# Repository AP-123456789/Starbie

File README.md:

# Starbie

Starbie is a custom embedded electronics project built around the Seeed Studio XIAO ESP32-C3 (RISC-V). It combines a Seeed XIAO ESP32-C3, a DHT11 temperature and humidity sensor, an MPU6050 IMU, a 0.96-inch I2C OLED display, and two push buttons on a custom two-layer PCB designed from scratch in KiCad.

## Hardware Components

* **Microcontroller:** [Seeed Studio XIAO ESP32-C3](https://wiki.seeedstudio.com/SeeedStudio_XIAO_ESP32C3/) (RISC-V 32-bit RISC-V single-core CPU, Wi-Fi, BLE)
* **Display:** 0.96-inch I2C Monochrome OLED Display (128x64 resolution, SSD1306 driver)
* **Temperature/Humidity Sensor:** [DHT11 Sensor](https://www.component101.com/sensors/dht11-temperature-and-humidity-sensor) with a $10\text{ k}\Omega$ pull-up resistor on the data line
* **Motion Sensor:** MPU6050 6-axis Accelerometer & Gyroscope
* **User Input:** 2x Tactile push buttons
* **Expansion:** 1x4 and 1x8 pin headers

## Repository Structure

```
starbie/
├── Firmware/
│   ├── include/
│   ├── lib/
│   ├── src/
│   │   └── main.cpp          # Core C++ firmware
│   └── platformio.ini        # PlatformIO build configuration
├── Hardware/
│   ├── startbie.kicad_sch    # Schematic capture file
│   ├── startbie.kicad_pcb    # PCB layout file
│   ├── startbie.kicad_pro    # KiCad project file
│   └── Gerbers/              # Manufacturing files
└── README.md
```

## Firmware & Toolchain

The firmware is written in C++ using the Arduino framework via PlatformIO in VS Code. It handles I2C communication with the OLED display while polling the push buttons and reading sensor data.

### Dependencies
* [Adafruit SSD1306 Library](https://github.com/adafruit/Adafruit_SSD1306)
* [Adafruit GFX Library](https://github.com/adafruit/Adafruit-GFX-Library)

---

## 10-Hour Build Log

### Hour 1: Environment Setup and Error 10013
I started by setting up a PlatformIO workspace for the ESP32-C3, referencing the [Seeed Studio XIAO ESP32-C3 Wiki](https://wiki.seeedstudio.com/SeeedStudio_XIAO_ESP32C3/). Right away, the build crashed with `Error 10013: An attempt was made to access a socket in a way forbidden by its access permissions`. 

After trying admin mode and checking firewalls with having no success, I looked through [PlatformIO Community Forum Discussions and GitHub Issues](https://community.platformio.org/) and realized local network security was blocking the registry port. Changing the package mirror source and clearing the local cache fixed the socket block and let dependencies download.

### Hours 2–4: Firmware Architecture
I wrote the core application logic in `Firmware/src/main.cpp`, integrating the [Adafruit SSD1306 Library](https://github.com/adafruit/Adafruit_SSD1306) and [Adafruit GFX Library](https://github.com/adafruit/Adafruit-GFX-Library). Compiling for the RISC-V architecture taught me a lot about managing memory and library conflicts before successfully generating the binary image, which I initially did not understand.

### Hours 5–7: Schematic Design
Transitioning to the hardware, I opened KiCad (`startbie.kicad_sch`) and placed the XIAO ESP32-C3 (`U2`), DHT11 (`U1`), push buttons (`SW1`, `SW2`), pin headers (`J1`, `J2`), and the $10\text{ k}\Omega$ pull-up resistor (`R1`) based on the [DHT11 Datasheet](https://www.component101.com/sensors/dht11-temperature-and-humidity-sensor).

I learned why pull-up resistors are needed for digital single-wire data lines and how power flags (`+3.3V`, `+5V`, `GND`) work.

Running the Electrical Rules Checker (ERC) helped catch floating pins before moving to the board layout.

### Hours 8–9.5: Footprints, Layout, and DRC
Updating the PCB layout from the schematic (referencing the [KiCad Getting Started Guide](https://docs.kicad.org/)) threw missing-footprint errors because default symbols weren't bound to physical packages.

I used the Assign Footprints tool to map symbols to their exact physical packages.

I hit a few search misses at first...

...but after fixing library paths, I found the correct packages (`Sensor:Aosong_DHT11` and `Seeed_Studio_XIAO_Series:XIAO-ESP32-C3-SMD`).

Then I initialized the PCB canvas in `startbie.kicad_pcb`...

...placed the components...

...and routed the copper traces on the top (`F.Cu`, red) and bottom (`B.Cu`, blue) layers.

When I ran the Design Rules Checker (DRC), it flagged 20 warnings.

I had to fix courtyard errors, widen traces that were under $0.2000\text{ mm}$, and clear silkscreen text overlapping solder masks.

### Hour 10: Gerbers and GitHub
With a clean DRC check, I generated manufacturing files and inspected them in the KiCad Gerber Viewer.

Finally, I added a `.gitignore`, initialized git, and pushed the repo to GitHub.

## 2-Hour Product Personalization

### Hours 11–12: DHT11 Climate Alert Integration & OLED UI Overhaul

I updated the Starbie firmware by adding a temperature and humidity alert system using the DHT11 sensor. The system monitors temperature and humidity and triggers warnings when the temperature exceeds 30°C or humidity exceeds 70%. I also updated the OLED Stats screen to display the sensor readings and corresponding warning messages. If both values exceed their limits, the display indicates both alerts; if the sensor readings are unavailable, it shows “Climate unavailable.” The updated firmware compiled successfully in PlatformIO, confirming that there were no compilation errors.

---

## BOM

| REFERENCE | VALUE | QUANTITY | DESCRIPTION |
| :--- | :--- | :--- | :--- |
| U2 | XIAO ESP32-C3 | 1 | Main microcontroller |
| U1 | DHT11 | 1 | Temperature and humidity sensor |
| SW1 | Push Button | 1 | User input button |
| SW2 | Push Button | 1 | User input button |
| R1 | 10k Ohm | 1 | Resistor |
| J1 | 4-pin connector | 1 | Power and I²C connections |
| J2 | 8-pin connector | 1 | Component connections |

## References

* [Seeed Studio XIAO ESP32-C3 Wiki](https://wiki.seeedstudio.com/SeeedStudio_XIAO_ESP32C3/)
* [PlatformIO Community Forums](https://community.platformio.org/)
* [Adafruit SSD1306 Library](https://github.com/adafruit/Adafruit_SSD1306)
* [Adafruit GFX Library](https://github.com/adafruit/Adafruit-GFX-Library)
* [DHT11 Sensor Datasheet](https://www.component101.com/sensors/dht11-temperature-and-humidity-sensor)
* [KiCad Documentation](https://docs.kicad.org/)

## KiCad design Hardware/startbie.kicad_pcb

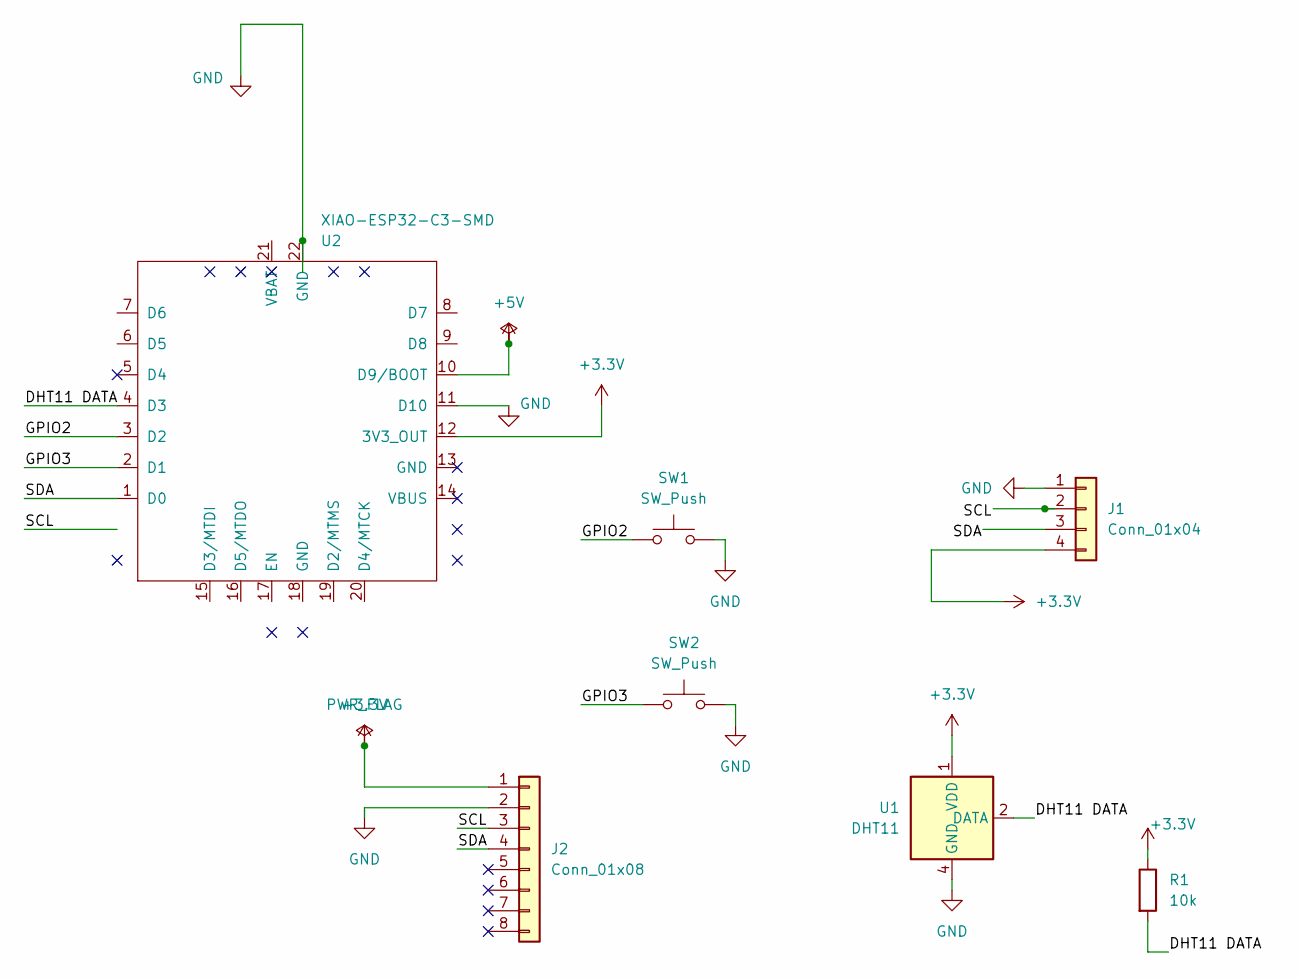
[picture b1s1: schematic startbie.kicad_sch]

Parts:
J1: Conn_01x04; Display_128x64_096_I2C
J2: Conn_01x08; MPU6050_Module
R1: 10k; R_Axial_DIN0207_L6.3mm_D2.5mm_P7.62mm_Horizontal
SW1, SW2: SW_Push; SW_Cherry_MX_1.00u_PCB
U1: DHT11; Aosong_DHT11_5.5x12.0_P2.54mm
U2: XIAO-ESP32-C3-SMD

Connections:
+3.3V: J1.4, J2.1, R1.1, U1.1 (VDD), U2.12 (3V3_OUT)
+5V: U2.10 (D9/BOOT)
/DHT11 DATA: R1.2, U1.2 (DATA), U2.4 (D3)
/GPIO2: SW1.1, U2.3 (D2)
/GPIO3: SW2.1, U2.2 (D1)
/SCL: J2.3
/SDA: J2.4, U2.1 (D0)
GND: J1.1, J2.2, SW1.2, SW2.2, U1.4 (GND), U2.11 (D10), U2.22 (GND)

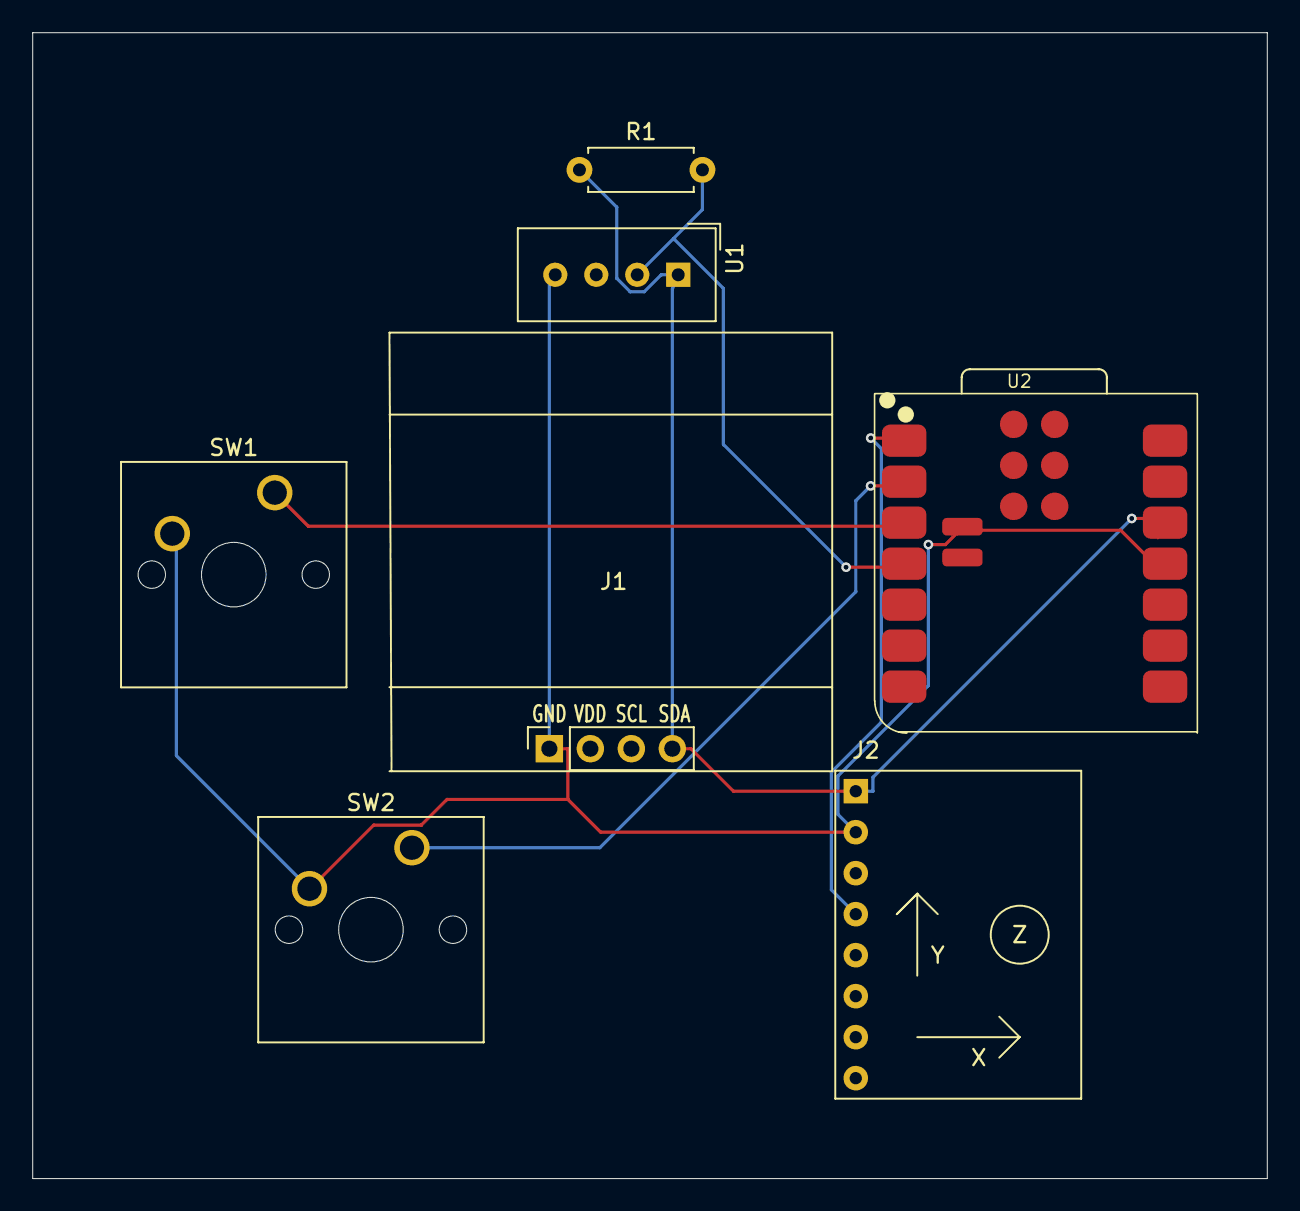
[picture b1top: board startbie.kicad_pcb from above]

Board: 2 copper layers, 76.5 x 71.0 mm, 7 parts (0 on the bottom side), 6 nets.
